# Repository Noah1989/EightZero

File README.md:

EightZero
=========

This project is an 8-bit microcomputer kit using modern hardware.

If you read this, you are awesome.

There is lots to do, such as writing this README...

Until then, just ask me: stefan@noack-software.de

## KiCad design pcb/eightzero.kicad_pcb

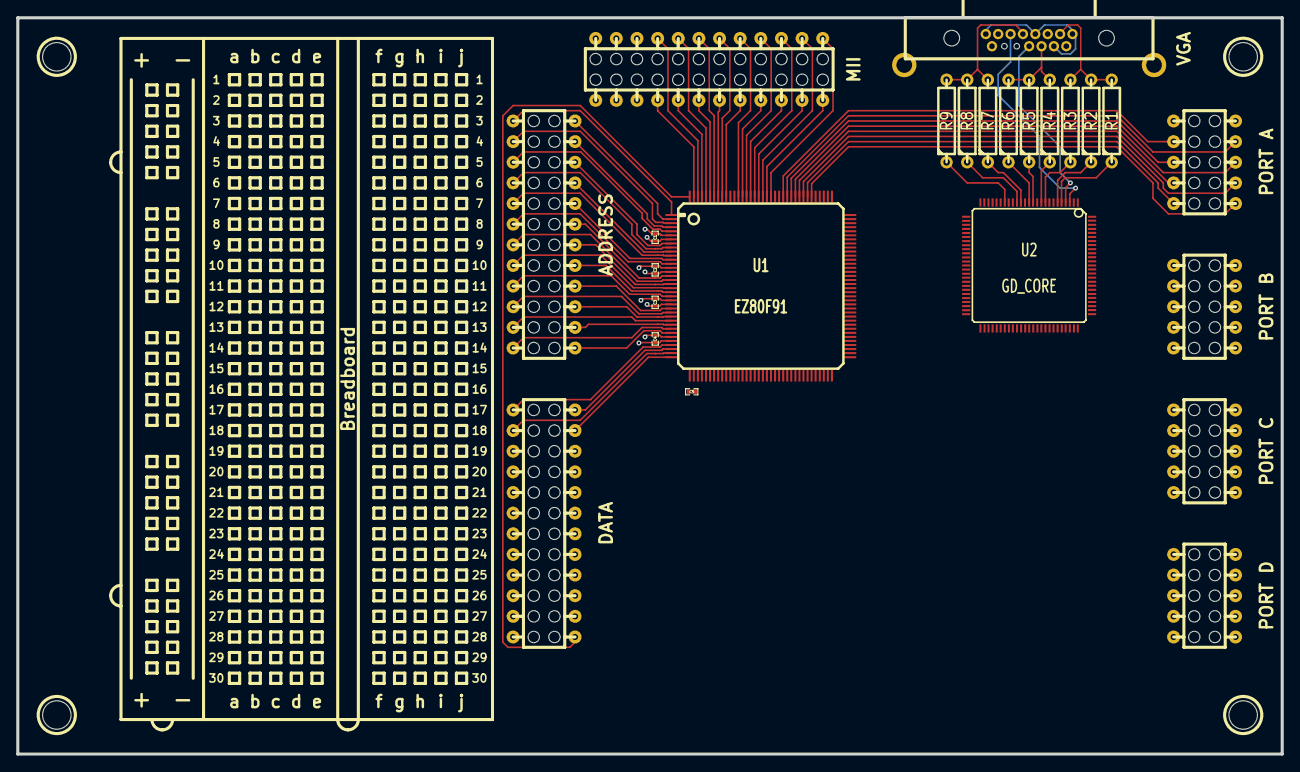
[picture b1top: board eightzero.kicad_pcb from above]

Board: 2 copper layers, 155.6 x 90.6 mm, 25 parts (0 on the bottom side), 114 nets.

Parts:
Breadboard: Breadboard
C1, C2, C3, C4, C5: SM0402
J1: VGA; EDAC_15
P1: ADDRESS; 71991-312LF
P2: DATA; 71991-312LF
P3: PORT A; 71991-305LF
P4: PORT B; 71991-305LF
P5: PORT C; 71991-305LF
P6: PORT D; 71991-305LF
P7: MII; 71991-312LF
R1, R2, R3, R4, R5, R6, R7, R8, R9: R; R4
U1: EZ80F91; TQFP144
U2: GD_CORE; TQFP_100

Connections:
+3.3V: C1.1, C2.1, C3.1, C4.1, C5.1, U1.6, U1.14, U1.22, U1.31, U1.37, U1.47, U1.59, U1.81, U1.88, U1.98, U1.112, U1.122, U1.133
/A0: P1.1, U1.1
/A1: P1.2, U1.2
/A2: P1.3, U1.3
/A3: P1.4, U1.4
/A4: P1.5, U1.5
/A5: P1.6, U1.8
/A6: P1.7, U1.9
/A7: P1.8, U1.10
/A8: P1.9, U1.11
/A9: P1.10, U1.12
/A10: P1.11, U1.13
/A11: P1.12, U1.16
/A12: P1.13, U1.17
/A13: P1.14, U1.18
/A14: P1.15, U1.19
/A15: P1.16, U1.20
/A16: P1.17, U1.21
/A17: P1.18, U1.24
/A18: P1.19, U1.25
/A19: P1.20, U1.26
/A20: P1.21, U1.27
/A21: P1.22, U1.28
/A22: P1.23, U1.29
/A23: P1.24, U1.30
/BLUE: J1.3, R7.2, R8.2, R9.2
/BUSACK: P2.22, U1.58
/BUSREQ: P2.21, U1.57
/CS0: P2.1, U1.33
/CS1: P2.2, U1.34
/CS2: P2.3, U1.35
/CS3: P2.4, U1.36
/D0: P2.5, U1.39
/D1: P2.6, U1.40
/D2: P2.7, U1.41
/D3: P2.8, U1.42
/D4: P2.9, U1.43
/D5: P2.10, U1.44
/D6: P2.11, U1.45
/D7: P2.12, U1.46
/GREEN: J1.2, R4.2, R5.2, R6.2
/HALT: P2.23, U1.65
/HSYNC: J1.13, U2.4
/INSTRD: P2.17, U1.53
/IORQ: P2.13, U1.49
/MREQ: P2.14, U1.50
/NMI: P2.20, U1.56
/RD: P2.15, U1.51
/RED: J1.1, R1.2, R2.2, R3.2
/RESET: P2.19, U1.55
/VSYNC: J1.14, U2.3
/WAIT: P2.18, U1.54
/WP: P2.24, U1.144
/WR: P2.16, U1.52
GND: C1.2, C2.2, C3.2, C4.2, C5.2, J1.5, J1.6, J1.7, J1.8, J1.10, U1.7, U1.15, U1.23, U1.32, U1.38, U1.48, U1.60, U1.64, U1.72, U1.82, U1.89, U1.99, U1.108, U1.113, U1.123, U1.134
unnamed: P3.2, U1.115
unnamed: P3.4, U1.117
unnamed: P3.6, U1.119
unnamed: P3.8, U1.121
unnamed: P4.8, U1.107
unnamed: P4.6, U1.105
unnamed: P4.4, U1.103
unnamed: P4.2, U1.101
unnamed: P6.8, U1.80
unnamed: P6.6, U1.78
unnamed: P5.4, U1.93
unnamed: P4.1, U1.100
unnamed: P4.3, U1.102
unnamed: P4.5, U1.104
unnamed: P4.7, U1.106
unnamed: P5.7, U1.96
unnamed: P5.5, U1.94
unnamed: P5.3, U1.92
unnamed: P5.1, U1.90
unnamed: P5.2, U1.91
unnamed: P5.6, U1.95
unnamed: P5.8, U1.97
unnamed: P6.7, U1.79
unnamed: P6.5, U1.77
unnamed: P6.3, U1.75
unnamed: P6.1, U1.73
unnamed: P6.2, U1.74
unnamed: P6.4, U1.76
unnamed: R6.1, U2.13
unnamed: R7.1, U2.15
unnamed: R8.1, U2.16
unnamed: R9.1, U2.19
unnamed: P7.18, U1.143
unnamed: R1.1, U2.5
unnamed: P7.17, U1.142
unnamed: R2.1, U2.6
unnamed: R3.1, U2.9
unnamed: R4.1, U2.10
unnamed: R5.1, U2.12
unnamed: P3.1, U1.114
unnamed: P3.3, U1.116
unnamed: P7.6, U1.129
unnamed: P7.9, U1.132
unnamed: P7.10, U1.135
unnamed: P7.12, U1.137
unnamed: P7.11, U1.136
unnamed: P7.15, U1.140
unnamed: P7.16, U1.141
unnamed: P7.14, U1.139
unnamed: P7.13, U1.138
unnamed: P7.5, U1.128
unnamed: P7.8, U1.131
unnamed: P7.7, U1.130
unnamed: P7.3, U1.126
unnamed: P7.4, U1.127
unnamed: P7.2, U1.125
unnamed: P7.1, U1.124
unnamed: P3.7, U1.120
unnamed: P3.5, U1.118

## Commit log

2012-12-26 some code for video initialization
2012-12-26 Test
2012-12-26 Some improvements, completed SPI initialization sequence.
2013-01-05 moved code to z88dk/z80asm
2013-01-05 minor format changes
2013-01-05 minor
2013-01-05 comments
2013-01-06 added simple visual studio solution for editing, minor changes
2013-01-06 syntax and formatting adjustments
2013-01-24 Fixed typo
2013-01-30 added sources for simple ZDI debugger
2013-01-30 added kicad project (pcb), moved code to src
2013-01-30 added some READMEs
2013-01-30 implemented bin2ram script
2013-01-30 added 'program' target to Makefile
2013-01-31 fixed spelling in README file name ;-)
2013-02-01 implemented basic video interface
    * ioutil.asm: renamed outseq to output_sequenve for clarity
    * main.asm: added SP initialization
    * video.asm: added a lot of code (loosely inspired by the GD library)
2013-02-01 Hello, world!
    * video.asm: hide sprites on reset
    * main.asm: now prints "Hello, world!" on screen :)
2013-02-01 Removed kicad project file. It's not necessary (yet?) and just messes up the language statistics.
2013-02-04 Implemented colored hex digits for machine code monitor
    * main.asm: some test code to show the digits
    * video.asm: added more symbols for external use
    * hexdigits.asm: this is the new code ;-)
2013-02-04 Some premature optimization ;-)
    Moved the call to video_spi_wait before the writes.
    Otherwise SPI would not operate asynchronously at all.
2013-02-04 Minor syntax changes.
    OR A, C is more readable than just OR C
2013-02-05 added .video_spi_write_A shortcut to directly send the value in A to the video device
2013-02-05 machine code monitor now shows a hexdump :)
    * Makefile: added new files
    * hexdigits.asm: XREFs before XDEFs for consistency
    * linechars.asm: new file, implements solid square characters
    * main.asm: removed test code, jump into monitor
    * monitor.asm: new file, implemented hex listing
    * video.asm: some XDEFs, changed default background color
2013-02-06 keyboard driver: interrupt vector initialization
2013-02-07 keyboard: finished initialization, work on interrupt routine
    The keyboard_isr now gets called on every incoming bit.
    * Makefile: added keyboard.asm
    * main.asm: added call to keyboard_init and enable interrupts
    * keyboard.asm: see comment above
2013-02-08 implemented: read data from the keyboard; next: decode and buffer
    *keyboard.asm: implemented serial read (no framing error detection!)
    *main.asm: some test code to see if there is data being received
2013-02-08 minor change: fixed case for constant
2013-02-11 keyboard: implemented frame error detection and reserved 4 status bits for the scancode decoding routine (which has yet to be implemented)
    Isn't it nice how we can fit all the data needed by the keyboard driver
    into two bytes? This means we can just stuff it all into the small unused
    space behind the interrupt vector. This has the advantage that no other
    memory needs to be reserved for the keyboard driver. The only restriction
    is that the interrupt vector table has to be in RAM, which is a good idea
    anyways. Another restriction is that the keyboard driver cannot run in ADL
2013-02-12 implemented scancode decoding
2013-02-12 added single byte write routines, renamed spi_write to spi_transmit
2013-02-12 small test program: print typed characters on screen.
2013-02-12 removed some duplicate code (whoops...)
2013-02-12 removed leftover comment
2013-02-13 cleaned up code, repaired single byte video write
2013-02-13 updated solution file
2013-02-13 updated visual studio solution
2013-02-13 simplified some code in hexdigits.asm
2013-02-13 implemented page scrolling and address indicator
2013-02-14 Fixed scan code tables (F1 was missing)
2013-02-15 fancy borders
2013-02-15 made borders even more pretty, added menu text
2013-02-18 added monitor help dialog
    * keyboard.asm: exported K_F1
    * linechars.asm: more colors!
    * monitor.asm: new help dialog
    * uitools.asm: new fancy box drawing
    * video.asm: changed screen clear character to space
2013-02-19 minor palette tweak
2013-02-19 added symbols (arrows) and more help screen text
    Printing the lines one by one is repetitive,
    there should be a better solution,
    like a function that prints strings and handles newlines.
    The green square in the help screen is a placeholder for a pretty icon.
2013-02-21 improved bin2ram speed, moved "tools" to "tool"
2013-02-21 simplified help dialog string printing
    print_string now makes it much easier to print multiple lines on screen
    I also refactored screen_locate out of the drawing functions
    because it's not needed for hard-coded top/left coordinates.
2013-02-23 implemented cursor, memory editing and calling
2013-02-23 removed unused code
    There's no need to keep this piece of code
    not only is it not needed anymore, it was also
    very badly written. It could have been implemented
    _much_ better like this (not tested):
    LD IYH, 0
    LD IYL, E
2013-03-01 added gfx sources
    icons for help dialog and load window
2013-03-04 added binary sprite data generator script
2013-03-05 save 1 byte and 1 cycle. yeah...
    Premature optimization is the root of all evil. And I'm very evil.
    http://wikiti.brandonw.net/index.php?title=Z80_Optimization
2013-03-05 added help dialog icon, hide cursor
2013-03-10 updated Makefile to generate .def files, removed .sln file
2013-03-12 improved .def file generation, moved externally visible constants to .inc files
2013-04-09 implemented loader menu user interface
2013-04-12 implemented serial receive and transmit
2013-04-12 loader input loop: now polls both serial interface and keyboard
2013-04-16 loader now accepts data
2013-04-17 bin2ram.py now supports the loader program
2013-04-18 bin2ram: close file to flush all data before printing "Done."
2013-04-18 loader now has a working progress bar, added math.asm for division
2013-04-20 changed PCB dimensions
2013-04-21 PCB: component placement, routing
2013-04-30 loader shows remaining byte count; fixed progress bar
2013-04-30 added menu item; minor color changes; reordered code in Makefile
2013-05-11 made SPI driver independent from video, added files for sdhc support
2013-05-14 minor formatting improvements, added Z80 identifier to asm sources
2013-05-18 rewrote SPI to use interrupts, implemented SDHC card detection and idle command
2013-05-26 sdhc init and block read
2013-05-26 fixed some errors
2013-06-01 updated python scripts to always use python2
2013-06-01 fixed SDHC initialization, block read seems to work now
2013-06-07 removed -e from Makefile
2013-06-08 implemented flash ROM access
2013-06-11 added documentation
2013-06-11 corrections, source formatting
2013-06-11 added some LaTeX semantics, minor corrections
2013-06-11 formatting, added ASCII table
2013-06-25 erste Erklärung zu Assembler
2013-06-25 Erste Erklärung zu Assembler Update
2013-06-25 documentation: corrections, formatting
2013-06-25 added figure (components, simplified)
2013-07-13 read MBR (test)
2013-07-13 improved initialization routine
2013-07-13 fat32 initialization: read MBR, VBR, find FAT and first cluster
2013-07-19 file system: list root directory
2013-07-19 improved transition between monitor and file manager
2013-07-19 fileman.asm: reordered initializations
2013-07-20 fat32.asm: removed code that adds redundant zero byte
    The zero byte is already included in the file name
    but may be followed by some $FF bytes for padding.
2013-07-22 fileman: menu, borders
2013-07-23 added kicad project and cmp-mod files
2013-07-25 pcb: minor rearrangements, added VGA port in schematic
2013-07-25 überarbeitung
2013-07-25 added charmap
2013-07-25 completed charmap
2013-07-26 implemented charmap converter tool, charmap loader WIP
2013-07-26 added charmap loader
2013-07-26 added missing files
2013-07-27 implemented charmap loader, added atari charmap
2013-07-27 minor color adjustment
2013-07-27 der maschinencode
2013-07-28 added characters to atari charmap, fixed draw_box
2013-07-28 ignore .DS_Store
2013-07-29 charmap
2013-07-29 added alpha channel
2013-07-29 another charmap
2013-07-29 fixed charmap
2013-07-29 fixed 6 glyph
2013-07-29 improved 1 glyph
2013-07-29 made 0 better distinguishable from 8
2013-07-29 rounded all glyphs to improve readability
2013-07-30 color, glyphs and symbols
2013-07-30 symbols
2013-07-30 fixed png2bin script
2013-07-30 added line drawing characters, improved f and t glyphs
2013-07-30 color change
2013-07-31 fixed loader
2013-07-31 disable interrupts for better warm reset
2013-08-03 new monitor screen
2013-08-08 Überabeitung und Erklärung des Speichers
2013-08-18 WIP monitor (temporarily disabled some init functions)
2013-08-18 monitor: fixed cursor, added byte inspector (bits and char)
2013-08-23 monitor: completed byte inspector; increment/decrement byte keys
2013-08-23 monitor: register viewer
2013-08-25 monitor: implemented trampoline / register analysis
2013-08-25 minor bugfix (+/- keys)
2013-08-26 monitor: show individual flag bits
2013-08-31 improved monitor: no flicker on redraw
2013-09-08 Verbesserung der Formulierung
2013-10-09 minor changes for current ROM version
2013-10-09 track ripup, new connector placement
2013-10-09 added debug signal to keyboard
2013-10-10 increased keyboard interrupt priority
2013-10-10 fixed typo in comment
2013-10-22 added VGA connector
2013-10-23 components, routing
2014-01-24 new fileman screen, list/select files
2014-01-25 editor: shows file content, cursor
2014-01-26 editor can now edit text, still kinda buggy
2014-01-26 minor bugfix (cursor not visible when going up)
2014-01-26 relocated code for ROM
2014-01-26 introducing zinu, the eZ80 ASM derivative of XINU
2014-01-27 completed queue data structure
2014-02-25 Den Maschiencode-Monitor verstehen
2014-04-07 added schematics for rs232 adapter and debugger board
2014-05-03 made kprintf putput something
2014-05-11 added a test runner
2014-05-22 added TEST DONE message
2014-05-22 added empty test for sprintf (should fail)
2014-05-22 fixed kprintf to restore IY, made test runner more robust against register trashing
2014-05-22 fixed some severe pointer confusion :)
2014-06-03 test for sprintf
